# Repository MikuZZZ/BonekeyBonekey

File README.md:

# BonekeyBonekey

Rose-Hulman Institute of Technology
32-bit Embeded Linux Final Project

Project Wiki page: http://elinux.org/ECE597_Fall_2014_Project_Bonekey_Bonekey

The idea come from Makey Makey by Jay Silver in Santa Cruz, CA
https://www.kickstarter.com/projects/joylabs/makey-makey-an-invention-kit-for-everyone

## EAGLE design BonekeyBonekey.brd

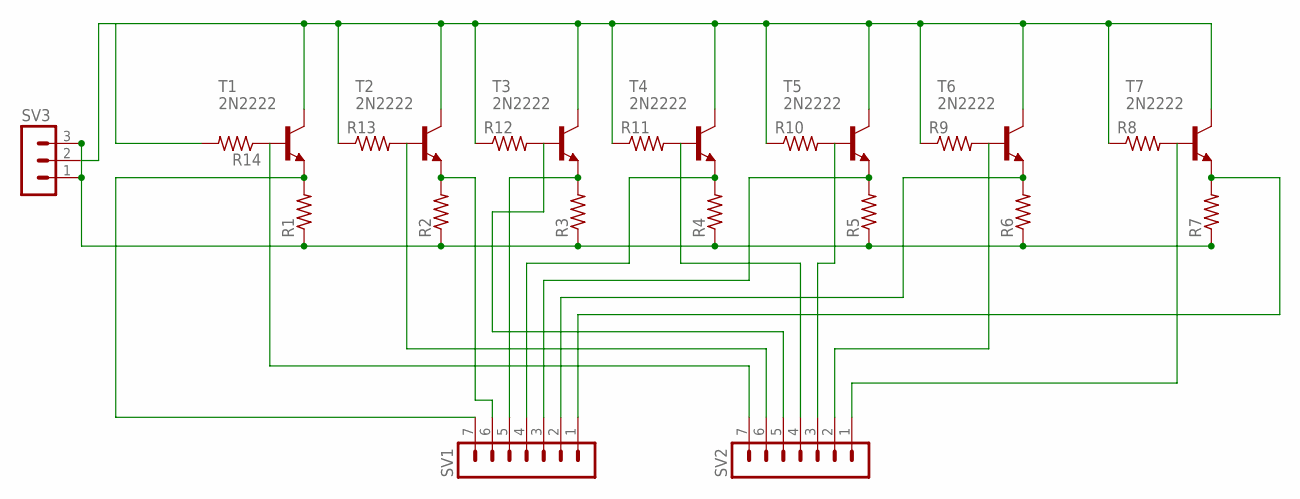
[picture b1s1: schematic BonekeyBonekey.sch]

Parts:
R1, R2, R3, R4, R5, R6, R7, R8, R9, R10, R11, R12, R13, R14: R-US_0204/5; 0204/5
SV1, SV2: MA07-1
SV3: MA03-1
T1, T2, T3, T4, T5, T6, T7: 2N2222; TO18

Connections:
unnamed: R14.1, SV2.7, T1.2 (B)
unnamed: R13.2, SV2.6, T2.2 (B)
unnamed: R12.2, SV2.5, T3.2 (B)
unnamed: R11.2, SV2.4, T4.2 (B)
unnamed: R10.2, SV2.3, T5.2 (B)
unnamed: R9.2, SV2.2, T6.2 (B)
unnamed: R8.2, SV2.1, T7.2 (B)
unnamed: R7.2, SV1.1, T7.1 (E)
unnamed: R6.2, SV1.2, T6.1 (E)
unnamed: R5.2, SV1.3, T5.1 (E)
unnamed: R4.2, SV1.4, T4.1 (E)
unnamed: R3.2, SV1.5, T3.1 (E)
unnamed: R2.2, SV1.6, T2.1 (E)
unnamed: R1.2, SV1.7, T1.1 (E)
unnamed: R8.1, R9.1, R10.1, R11.1, R12.1, R13.1, R14.2, SV3.2, T1.3 (C), T2.3 (C), T3.3 (C), T4.3 (C), T5.3 (C), T6.3 (C), T7.3 (C)
unnamed: R1.1, R2.1, R3.1, R4.1, R5.1, R6.1, R7.1, SV3.1, SV3.3

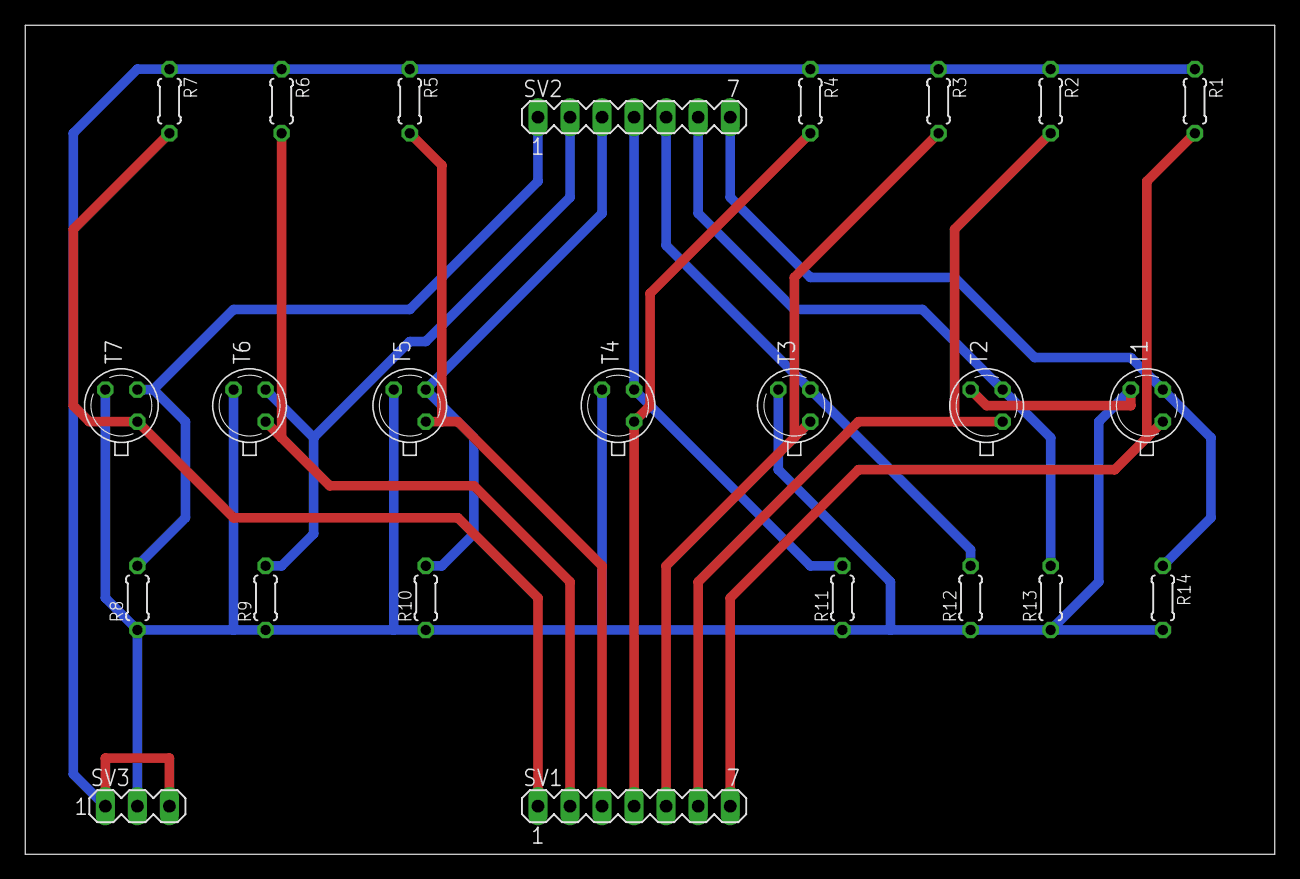
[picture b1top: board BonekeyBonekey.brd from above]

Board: 2 copper layers, 99.0 x 65.7 mm, 24 parts (0 on the bottom side), 16 nets.

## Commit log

2014-09-03 rename
2014-09-03 cleanup
2014-09-04 add asoundrc
2014-11-14 add schematic and board file
